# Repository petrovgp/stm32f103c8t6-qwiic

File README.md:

# STM32F103C8T6 Qwiic-Compatible Breakout Board

A compact and versatile **STM32F103C8T6** breakout board designed in **KiCad 9**, featuring multiple Qwiic-compatible connectors for easy sensor and peripheral integration. Ideal for prototyping, embedded development, and educational use.

## 📸 Board design

## 🧠 Features

### ⚡ Core
- **STM32F103C8T6** ARM Cortex-M3 microcontroller (72 MHz, 64 KB Flash, 20 KB RAM)
- Compact and breadboard-friendly **breakout board design**

### 🔋 Power System
- Operable from **3.3 V regulated** or **5 V external input**
- **ME6211C** LDO regulator:
  - 500 mA maximum output current  
  - 100 mV dropout at 100 mA load

### 🔗 Connectivity
- **Qwiic-compatible connectors** for easy plug-and-play I²C expansion:
  - **I²C1 Qwiic port**
  - **I²C2 Qwiic port**
  - **SWD Qwiic port** for programming and debugging
- Clearly labeled GPIO and power pins for easy interfacing

## 🧩 Design Files
All design files were created in **KiCad 9** and production files have been exported with **PCBWay plugin**:
- `schematics/` – full circuit schematics
- `kicad/` – KiCAD 9 project files 
- `kicad/production/` – ready-to-manufacture files (GERBERs + BOM)

Adjustment of production files might be needed. Please check carefully before placing any manufacturing orders.

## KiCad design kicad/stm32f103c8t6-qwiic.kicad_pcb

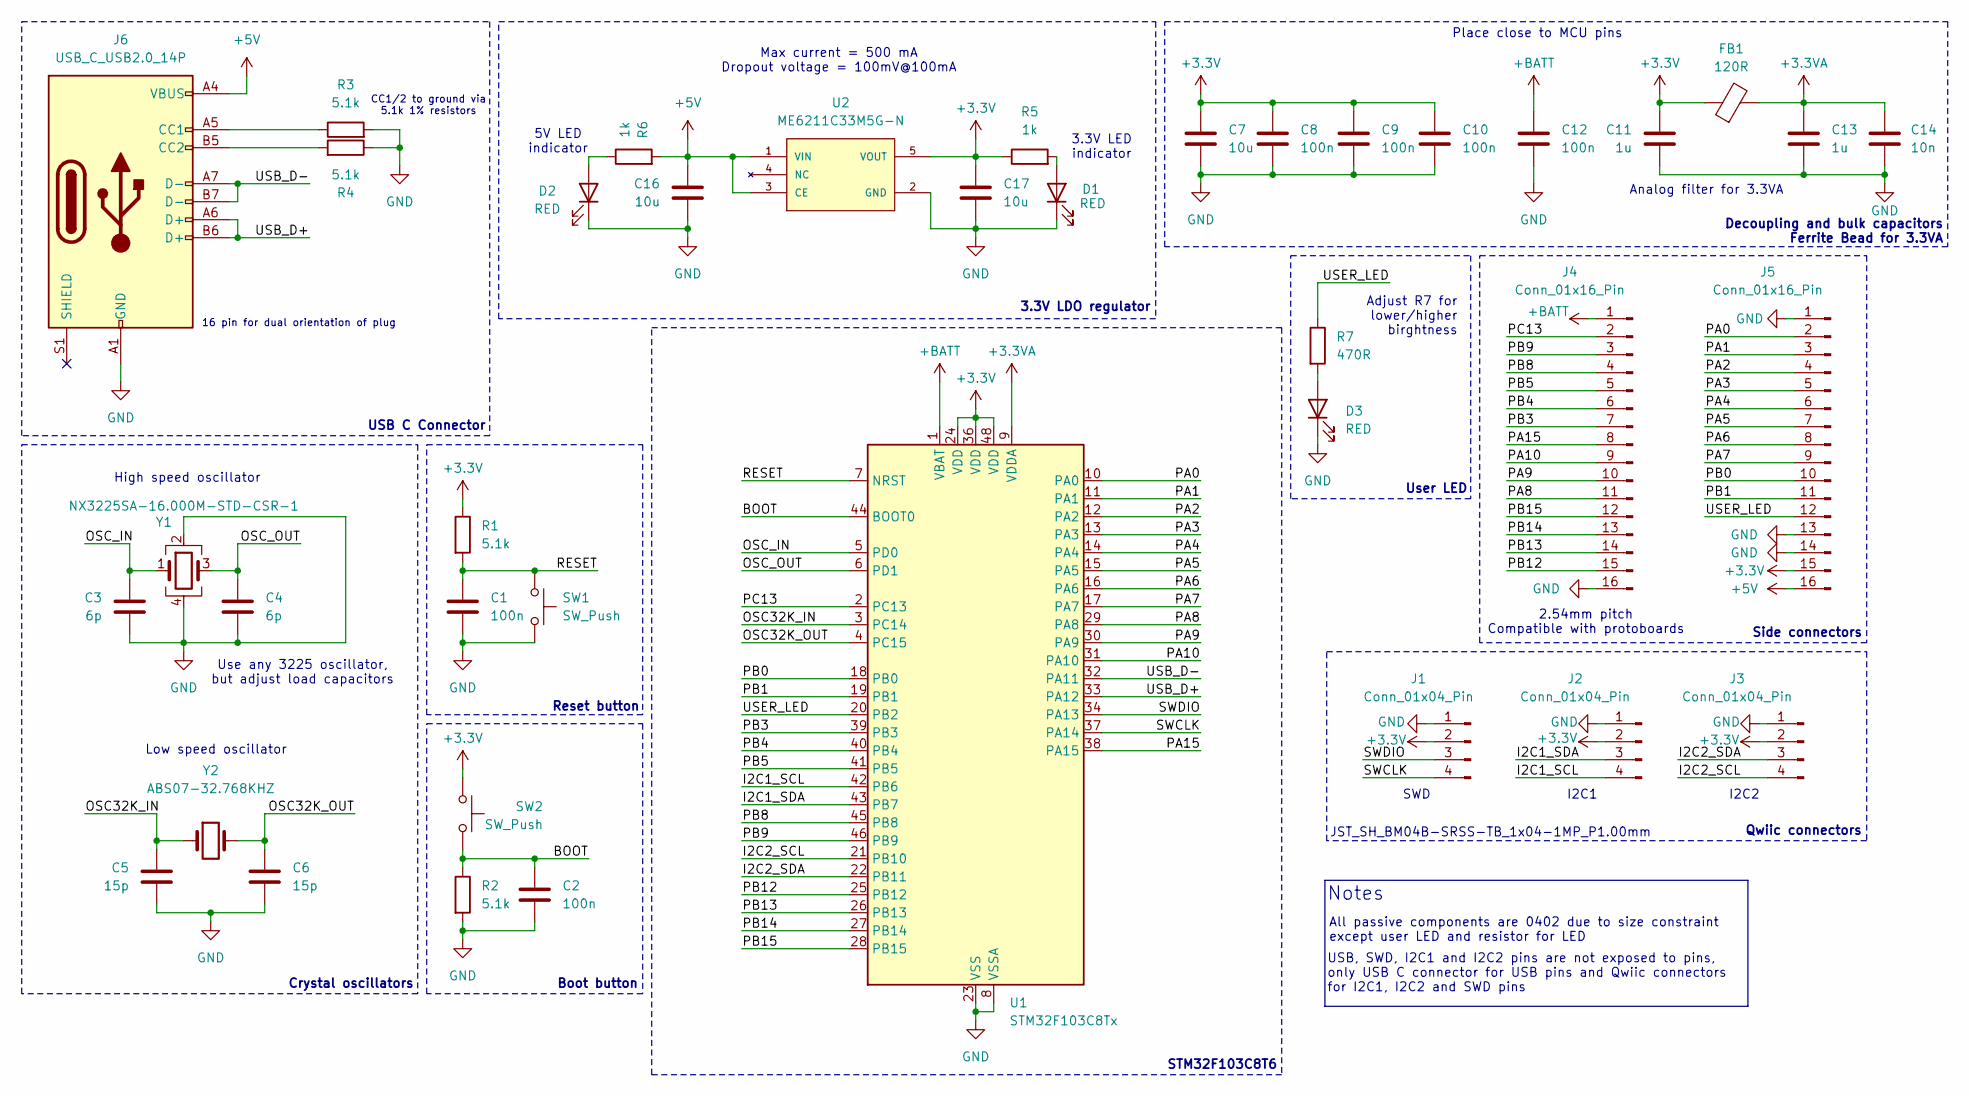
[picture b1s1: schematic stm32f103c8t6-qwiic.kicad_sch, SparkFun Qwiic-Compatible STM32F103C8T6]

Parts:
C1, C2, C8, C9, C10, C12: 100n; C_0402_1005Metric
C3, C4: 6p; C_0402_1005Metric
C5, C6: 15p; C_0402_1005Metric
C7, C16, C17: 10u; C_0402_1005Metric
C11, C13: 1u; C_0402_1005Metric
C14: 10n; C_0402_1005Metric
D1, D2: RED; LED_0402_1005Metric
D3: RED; C_0603_1608Metric
FB1: 120R; L_0402_1005Metric
J1, J2, J3: Conn_01x04_Pin; JST_SH_SM04B-SRSS-TB_1x04-1MP_P1.00mm_Horizontal
J4, J5: Conn_01x16_Pin; PinHeader_1x16_P2.54mm_Vertical
J6: USB_C_USB2.0_14P; USB_C_Receptacle_GCT_USB4105-xx-A_16P_TopMnt_Horizontal
R1, R2, R3, R4: 5.1k; R_0402_1005Metric
R5, R6: 1k; R_0402_1005Metric
R7: 470R; R_0603_1608Metric
SW1, SW2: SW_Push; SW_Push_1P1T_NO_CK_KMR2
U1: STM32F103C8Tx; LQFP-48_7x7mm_P0.5mm
U2: ME6211C33M5G-N; SOT-23-5
Y1: NX3225SA-16.000M-STD-CSR-1; Crystal_SMD_3225-4Pin_3.2x2.5mm
Y2: ABS07-32.768KHZ; Crystal_SMD_EuroQuartz_EQ161-2Pin_3.2x1.5mm

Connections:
+3.3V: C7.1, C8.1, C9.1, C10.1, C11.1, C17.1, FB1.1, J1.2, J2.2, J3.2, J5.15, R1.1, R5.1, SW2.2, U1.24 (VDD), U1.36 (VDD), U1.48 (VDD), U2.5 (VOUT)
+3.3VA: C13.1, C14.1, FB1.2, U1.9 (VDDA)
+5V: C16.1, J5.16, J6.A4 (VBUS), J6.A9 (VBUS), J6.B4 (VBUS), J6.B9 (VBUS), R6.2, U2.1 (VIN), U2.3 (CE)
+BATT: C12.1, J4.1, U1.1 (VBAT)
/BOOT: C2.1, R2.1, SW2.1, U1.44 (BOOT0)
/I2C1_SCL: J2.4, U1.42 (PB6)
/I2C1_SDA: J2.3, U1.43 (PB7)
/I2C2_SCL: J3.4, U1.21 (PB10)
/I2C2_SDA: J3.3, U1.22 (PB11)
/OSC32K_IN: C5.1, U1.3 (PC14), Y2.1
/OSC32K_OUT: C6.1, U1.4 (PC15), Y2.2
/OSC_IN: C3.1, U1.5 (PD0), Y1.1
/OSC_OUT: C4.1, U1.6 (PD1), Y1.3
/PA0: J5.2, U1.10 (PA0)
/PA1: J5.3, U1.11 (PA1)
/PA2: J5.4, U1.12 (PA2)
/PA3: J5.5, U1.13 (PA3)
/PA4: J5.6, U1.14 (PA4)
/PA5: J5.7, U1.15 (PA5)
/PA6: J5.8, U1.16 (PA6)
/PA7: J5.9, U1.17 (PA7)
/PA8: J4.11, U1.29 (PA8)
/PA9: J4.10, U1.30 (PA9)
/PA10: J4.9, U1.31 (PA10)
/PA15: J4.8, U1.38 (PA15)
/PB0: J5.10, U1.18 (PB0)
/PB1: J5.11, U1.19 (PB1)
/PB3: J4.7, U1.39 (PB3)
/PB4: J4.6, U1.40 (PB4)
/PB5: J4.5, U1.41 (PB5)
/PB8: J4.4, U1.45 (PB8)
/PB9: J4.3, U1.46 (PB9)
/PB12: J4.15, U1.25 (PB12)
/PB13: J4.14, U1.26 (PB13)
/PB14: J4.13, U1.27 (PB14)
/PB15: J4.12, U1.28 (PB15)
/PC13: J4.2, U1.2 (PC13)
/RESET: C1.1, R1.2, SW1.1, U1.7 (NRST)
/SWCLK: J1.4, U1.37 (PA14)
/SWDIO: J1.3, U1.34 (PA13)
/USB_D+: J6.A6 (D+), J6.B6 (D+), U1.33 (PA12)
/USB_D-: J6.A7 (D-), J6.B7 (D-), U1.32 (PA11)
/USER_LED: J5.12, R7.1, U1.20 (PB2)
GND: C1.2, C2.2, C3.2, C4.2, C5.2, C6.2, C7.2, C8.2, C9.2, C10.2, C11.2, C12.2, C13.2, C14.2, C16.2, C17.2, D1.1 (K), D2.1 (K), D3.1 (K), J1.1, J2.1, J3.1, J4.16, J5.1, J5.13, J5.14, J6.A1 (GND), J6.A12 (GND), J6.B1 (GND), J6.B12 (GND), R2.2, R3.2, R4.1, SW1.2, U1.8 (VSSA), U1.23 (VSS), U1.35 (VSS), U1.47 (VSS), U2.2 (GND), Y1.2, Y1.4
unnamed: D1.2 (A), R5.2
unnamed: D2.2 (A), R6.1
unnamed: D3.2 (A), R7.2
unnamed: J6.A5 (CC1), R3.1
unnamed: J6.B5 (CC2), R4.2

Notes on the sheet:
Reset button
Analog filter for 3.3VA
Low speed oscillator
I2C1
3.3V LED indicator
Place close to MCU pins
Adjust R7 for lower/higher birghtness
Boot button
SWD
CC1/2 to ground via 5.1k 1% resistors
Crystal oscillators
User LED
5V LED indicator
Decoupling and bulk capacitors Ferrite Bead for 3.3VA
USB, SWD, I2C1 and I2C2 pins are not exposed to pins, only USB C connector for USB pins and Qwiic connectors for I2C1, I2C2 and SWD pins
2.54mm pitch Compatible with protoboards
USB C Connector
STM32F103C8T6
3.3V LDO regulator
All passive components are 0402 due to size constraint except user LED and resistor for LED
Max current = 500 mA Dropout voltage = 100mV@100mA
16 pin for dual orientation of plug
Side connectors
Notes
High speed oscillator
I2C2
Use any 3225 oscillator, but adjust load capacitors
JST_SH_BM04B-SRSS-TB_1x04-1MP_P1.00mm
Qwiic connectors

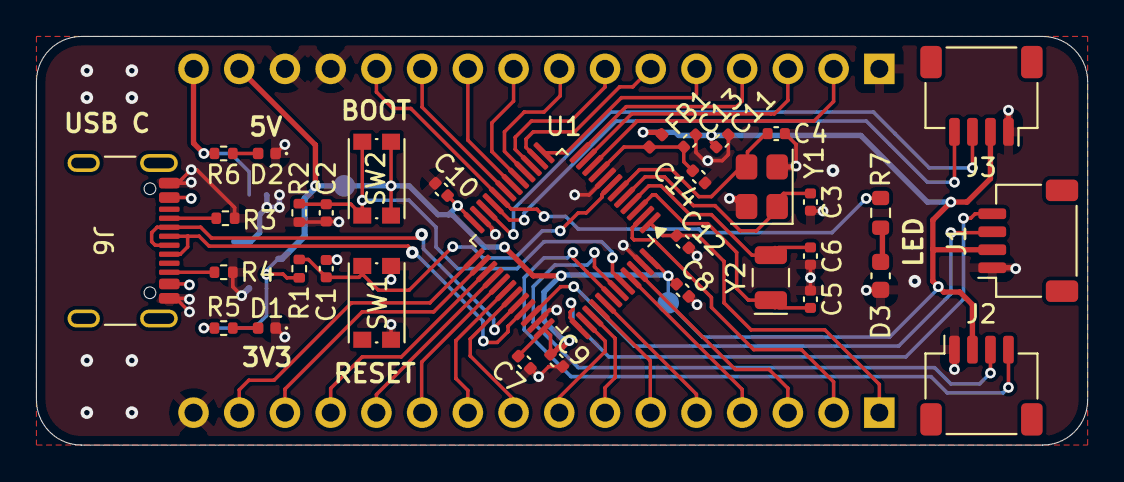
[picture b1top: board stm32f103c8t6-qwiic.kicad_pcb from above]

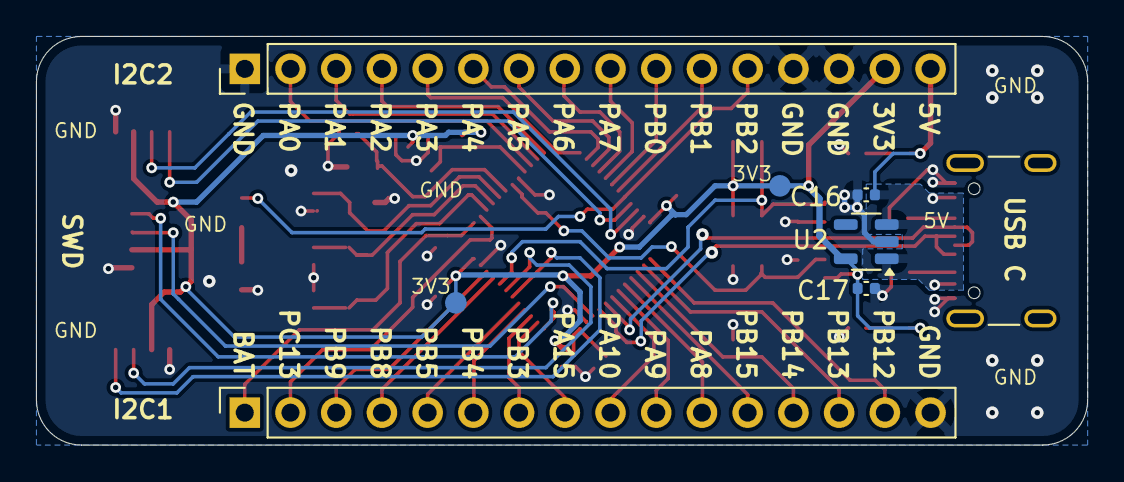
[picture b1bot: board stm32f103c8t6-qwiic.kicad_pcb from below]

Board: 2 copper layers, 58.4 x 22.7 mm, 39 parts (5 on the bottom side), 49 nets.

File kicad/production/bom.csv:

Designator,Footprint,Quantity,Value,LCSC Part #
"C1, C10, C12, C2, C8, C9",0402,6,100n,
"C11, C13",0402,2,1u,
C14,0402,1,10n,
"C16, C17, C7",0402,3,10u,
"C3, C4",0402,2,6p,
"C5, C6",0402,2,15p,
"D1, D2",0402,2,RED,
D3,0603,1,RED,
FB1,0402,1,120R,
"J1, J2, J3",JST_SH_SM04B-SRSS-TB_1x04-1MP_P1.00mm_Horizontal,3,SM04B-SRSS-TB_1x04-1MP_P1.00mm_Horizontal,
J6,USB_C_Receptacle_GCT_USB4105-xx-A_16P_TopMnt_Horizontal,1,USB_C_USB2.0_16P,
"R1, R2, R3, R4",0402,4,5.1k,
"R5, R6",0402,2,1k,
R7,0603,1,470R,
"SW1, SW2",SW_Push_1P1T_NO_CK_KMR2,2,SW_Push,
U1,LQFP-48_7x7mm_P0.5mm,1,STM32F103C8T6,
U2,SOT-23-5,1,ME6211C33M5G-N,
Y1,Crystal_SMD_3225-4Pin_3.2x2.5mm,1,NX3225SA-16.000M-STD-CSR-1,
Y2,Crystal_SMD_EuroQuartz_EQ161-2Pin_3.2x1.5mm,1,ABS07-32.768KHZ,

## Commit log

2025-10-22 Add board design images
2025-10-24 Add schematic
2025-10-24 Add KiCAD 9 project and production files
2025-10-24 Update KiCAD files due to wrong footprint BM04B was chosen instead of SM04B for the Qwiic connectors. This commit updates the footprints, layout and production files.
2025-11-09 Update production files
